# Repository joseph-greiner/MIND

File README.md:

# MIND: Modular-IN2-Nixie-Display
This is a modular display made for Russian IN2 Nixie tubes. Each display contains 2 tubes and 2 LED decimal places. These can be stacked up as many as you would like, as long as the high voltage supply can provide the necessary current to run them.<br>

Version 1:<br>
  Basic disply functionality achieved. Yay!<br>
  An example of the current progress is at https://youtu.be/8mW3LZJ6aFY <br>
  <b>TODO:</b>
  <ul>
    <li>Add a current limiting circuit to the module, ideally no more than 2mA should be supplied to each tube.</li>
    <li>Change the connection header so that the boards can be stacked easier. Perhaps add a header to each side of the board.</li>
    <li>Change the shift register so that each module can shift the data out to the next, not sure what I was thinking.</li>
    <li>Decide on a better plan for the decimal places, the current one is cludgy and I don't like it.</li>
  </ul>

Each module is built up from one shift register and two BCD to decimal IC's and discrete components. The cost of each individual module was a high priority for me, so I have done my best to keep them under $5 US. Which achievable depending upon where your PCB's are made.

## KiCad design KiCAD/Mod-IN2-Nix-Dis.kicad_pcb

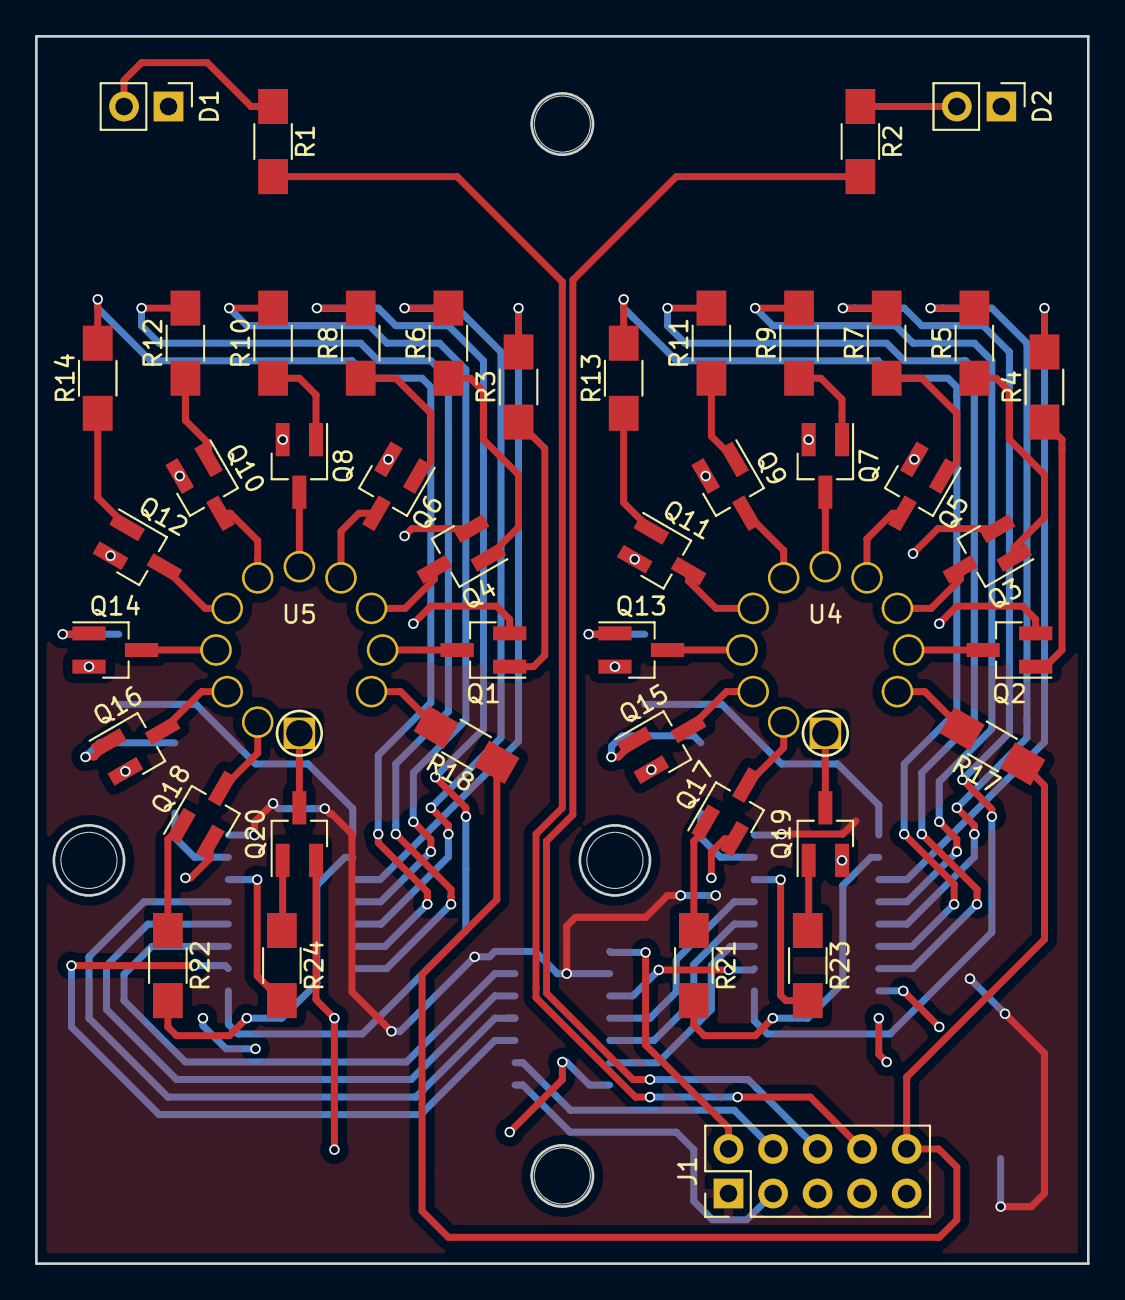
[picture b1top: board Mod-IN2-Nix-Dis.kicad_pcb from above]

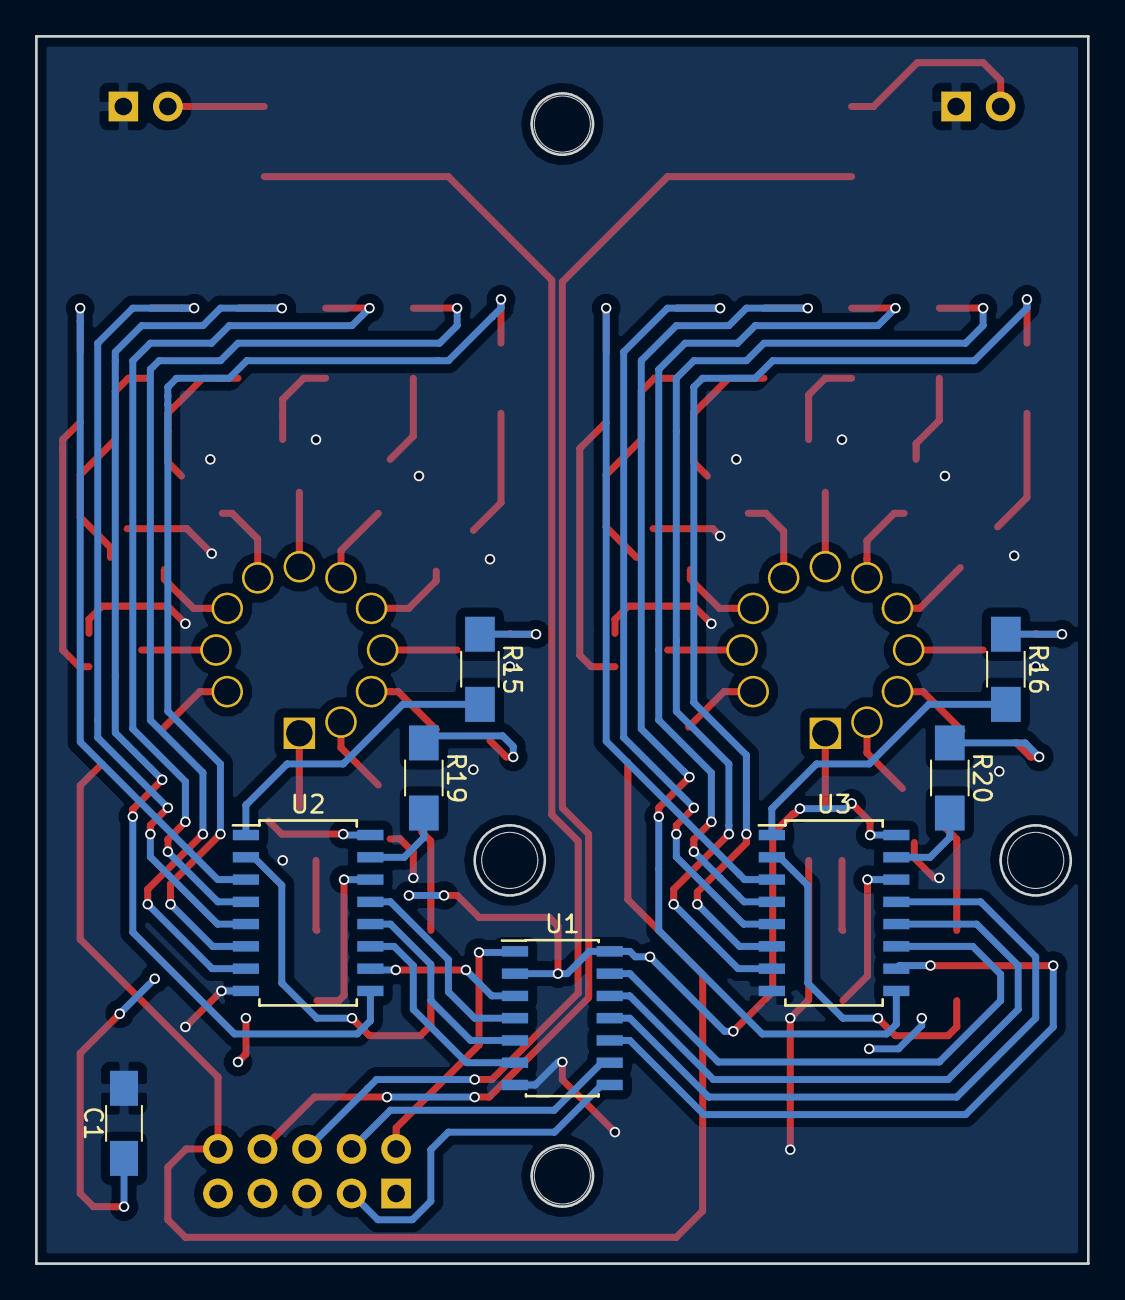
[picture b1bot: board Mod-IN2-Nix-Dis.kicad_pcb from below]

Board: 2 copper layers, 60.0 x 70.0 mm, 53 parts (8 on the bottom side), 80 nets.

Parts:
C1: 0.1uF; C_1206_HandSoldering
D1, D2: LED; Pin_Header_Straight_1x02_Pitch2.54mm
J1: Conn_02x05_Counter_Clockwise; Pin_Header_Straight_2x05_Pitch2.54mm
Q1, Q2, Q3, Q4, Q5, Q6, Q7, Q8, Q9, Q10, Q11, Q12, Q13, Q14, Q15, Q16, Q17, Q18, Q19, Q20: MMBTA42L; SOT-23_Handsoldering
R1, R2: 200; R_1206_HandSoldering
R3, R4, R5, R6, R7, R8, R9, R10, R11, R12, R13, R14, R15, R16, R19, R20, R21, R22, R23, R24: 15k; R_1206_HandSoldering
R17, R18: 22k; R_1206_HandSoldering
U1: 74HC164; SOIC-14_3.9x8.7mm_Pitch1.27mm
U2, U3: 4028; SOIC-16W_5.3x10.2mm_Pitch1.27mm
U4, U5: IN-2; Nixie-IN2

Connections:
+5V: C1.1, J1.1, U1.2, U1.14, U2.16, U3.16
+170VDC: J1.10, R17.1, R18.1
CLK: J1.3, U1.8
DATA: J1.2, U1.1
DIG_1_DEC: J1.8, R1.2
DIG_2_DEC: J1.6, R2.2
GND: C1.2, D1.1, D2.1, J1.5, Q1.2, Q2.2, Q3.2, Q4.2, Q5.2, Q6.2, Q7.2, Q8.2, Q9.2, Q10.2, Q11.2, Q12.2, Q13.2, Q14.2, Q15.2, Q16.2, Q17.2, Q18.2, Q19.2, Q20.2, U1.7, U2.8, U3.8
unnamed: D1.2, R1.1
unnamed: D2.2, R2.1
unnamed: Q1.1, R3.1
unnamed: Q1.3, U5.10
unnamed: Q2.1, R4.1
unnamed: Q2.3, U4.10
unnamed: Q3.1, R5.1
unnamed: Q3.3, U4.9
unnamed: Q4.1, R6.1
unnamed: Q4.3, U5.9
unnamed: Q5.1, R7.1
unnamed: Q5.3, U4.8
unnamed: Q6.1, R8.1
unnamed: Q6.3, U5.8
unnamed: Q7.1, R9.1
unnamed: Q7.3, U4.7
unnamed: Q8.1, R10.1
unnamed: Q8.3, U5.7
unnamed: Q9.1, R11.1
unnamed: Q9.3, U4.6
unnamed: Q10.1, R12.1
unnamed: Q10.3, U5.6
unnamed: Q11.1, R13.1
unnamed: Q11.3, U4.5
unnamed: Q12.1, R14.1
unnamed: Q12.3, U5.5
unnamed: Q13.1, R15.1
unnamed: Q13.3, U4.4
unnamed: Q14.1, R16.1
unnamed: Q14.3, U5.4
unnamed: Q15.1, R19.1
unnamed: Q15.3, U4.3
unnamed: Q16.1, R20.1
unnamed: Q16.3, U5.3
unnamed: Q17.1, R21.1
unnamed: Q17.3, U4.2
unnamed: Q18.1, R22.1
unnamed: Q18.3, U5.2
unnamed: Q19.1, R23.1
unnamed: Q19.3, U4.1
unnamed: Q20.1, R24.1
unnamed: Q20.3, U5.1
unnamed: R3.2, U3.3
unnamed: R4.2, U2.3
unnamed: R5.2, U2.5
unnamed: R6.2, U3.5
unnamed: R7.2, U2.9
unnamed: R8.2, U3.9
unnamed: R9.2, U2.4
unnamed: R10.2, U3.4
unnamed: R11.2, U2.7
unnamed: R12.2, U3.7
unnamed: R13.2, U2.6
unnamed: R14.2, U3.6
unnamed: R15.2, U2.1
unnamed: R16.2, U3.1
unnamed: R17.2, U4.11
unnamed: R18.2, U5.11
unnamed: R19.2, U2.15
unnamed: R20.2, U3.15
unnamed: R21.2, U2.2
unnamed: R22.2, U3.2
unnamed: R23.2, U2.14
unnamed: R24.2, U3.14
unnamed: U1.3, U2.10
unnamed: U1.4, U2.13
unnamed: U1.5, U2.12
unnamed: U1.6, U2.11
unnamed: U1.10, U3.10
unnamed: U1.11, U3.13
unnamed: U1.12, U3.12
unnamed: U1.13, U3.11
~CLR: J1.4, U1.9

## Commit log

2018-06-12 Update README.md
    Added version 1 information and TODO list for version 1.1
